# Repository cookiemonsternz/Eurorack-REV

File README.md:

# REV

_Digital reverb / delay eurorack module, user programmable and customisable._

#### What?
The next effect in a series of eurorack modules! REV is a custom digital reverb/delay processer, utilising the rp2040 mcu. Includes firmware for a basic algorithmic reverb, completely configurable via software. Default configuration uses 60kb of sram out of 264kb max. 

In terms of controls, REV features two potentiometers and 3 switches, which are by default configured to control reverb length and mix, with the switches adjusting brightness, density and stereo mixing.

#### Why?
Reverb is a very widely used effect, and arguably one of the most important in synthesizers. It sounds pretty cool but is unfortunately quite tricky to do completely analog. This module aims to provide a convenient and open source base to not only use as a reverb module, but also to prototype other digital effects.

I personally decided to make it due to my frustration with constantly having to lug around my laptop whenever I wanted reverb on my synth (which doesn't have an in-built fx section). A eurorack module is much more convenient. Having it be my own hardware allows for much more customisation than off the shelf modules / pedals, which I find very attractive.

#### How to use?
REV is a stereo board, it has an input and output for left and right, and the controls are all labelled.

In terms of getting it set up, you'll need to program the rp2040. To do this, bridge J4, which will allow you to program the flash, and then plug in the usb port. The rp2040 should show up as USB Mass Storage Device. Copy the uf2 file from the releases tab folder into the device and then disconnect J4 and unplug the usb. When you power it up via the eurorack power connector (not usb) the module should be functional.

## Renders

## Schematics

## Zine Page

## BOM
_Needed is how many I personally need :)_
| Part                                 | Quantity | Needed | Source     | Link                                                                      | Lot / Min Amount | Unit    | Net     | Running |
|--------------------------------------|----------|--------|------------|---------------------------------------------------------------------------|------------------|---------|---------|---------|
| **Capacitors**                           |          |        |            |                                                                           |                  |         |         |         |
| 100n Cap, 0805                       | 19       | 19     | JLCPCB     | https://jlcpcb.com/partdetail/YAGEO-CC0805KRX7R9BB104/C49678              | 1                | $0.0094 | $0.1786 | $0.18   |
| 1u Cap, 0805                         | 2        | 2      | JLCPCB     | https://jlcpcb.com/partdetail/29074-CL21B105KBFNNNE/C28323                | 1                | $0.0190 | $0.0380 | $0.22   |
| 10u Cap, 0805                        | 4        | 4      | JLCPCB     | https://jlcpcb.com/partdetail/16532-CL21A106KAYNNNE/C15850                | 1                | $0.0472 | $0.1888 | $0.41   |
| 47u Cap, 0805                        | 2        | 2      | JLCPCB     | https://jlcpcb.com/partdetail/17464-CL21A476MQYNNNE/C16780                | 1                | $0.0921 | $0.1842 | $0.59   |
| 10u Electrolytic Cap, D4.0xP1.5      | 2        | 0      | LCSC       | https://www.lcsc.com/product-detail/C88726.html                           | 10               | $0.0564 | $0.5600 | $1.15   |
| 22u Tantalum Cap, CASE-A-3216-18(mm) | 2        | 2      | LCSC       | https://www.lcsc.com/product-detail/C11366.html                           | 1                | $0.2379 | $0.4758 | $1.63   |
| **Resistors**                            |          |        |            |                                                                           |                  |         |         |         |
| 22? Resistor, 0805                   | 2        | 2      | JLCPCB     | https://jlcpcb.com/partdetail/18249-0805W8F220JT5E/C17561                 | 1                | $0.0027 | $0.0054 | $1.63   |
| 100? Resistor, 0805                  | 2        | 2      | JLCPCB     | https://jlcpcb.com/partdetail/18096-0805W8F1000T5E/C17408                 | 1                | $0.0023 | $0.0046 | $1.64   |
| 220? Resistor, 0805                  | 2        | 2      | JLCPCB     | https://jlcpcb.com/partdetail/18245-0805W8F2200T5E/C17557                 | 1                | $0.0031 | $0.0062 | $1.64   |
| 3.9k? Resistor, 0805                 | 2        | 2      | JLCPCB     | https://jlcpcb.com/partdetail/18302-0805W8F3901T5E/C17614                 | 1                | $0.0031 | $0.0062 | $1.65   |
| 10k? Resistor, 0805                  | 5        | 5      | JLCPCB     | https://jlcpcb.com/partdetail/18102-0805W8F1002T5E/C17414                 | 1                | $0.0029 | $0.0145 | $1.66   |
| 1M? Resistor, 0805                   | 2        | 2      | JLCPCB     | https://jlcpcb.com/partdetail/18202-0805W8F1004T5E/C17514                 | 1                | $0.0024 | $0.0048 | $1.67   |
| **Other**                                |          |        |            |                                                                           |                  |         |         |         |
| Schottky Diode, SOD-323              | 2        | 2      | JLCPCB     | https://jlcpcb.com/partdetail/GuangdongHottech-1N5819WS/C191023           | 1                | $0.0111 | $0.0222 | $1.69   |
| PJ301M-12 Jacks                      | 4        | 0      | Aliexpress | www.aliexpress.com/item/1005004864182675.html                             | 10               | $4.4000 | $0.0000 | $1.69   |
| RK09K 100k Potentiometer             | 2        | 0      | Aliexpress | https://www.aliexpress.com/item/1005007278123055.html                     | 5                | $1.0400 | $0.0000 | $1.69   |
| TL072CDT                             | 1        | 1      | JLCPCB     | https://jlcpcb.com/partdetail/STMicroelectronics-TL072CDT/C6961           | 1                | $0.1568 | $0.1568 | $1.85   |
| X322512MSB4SI 12MHz Crystal          | 1        | 1      | JLCPCB     | https://jlcpcb.com/partdetail/YXC_CrystalOscillators-X322512MSB4SI/C9002  | 1                | $0.0740 | $0.0740 | $1.92   |
| 74HC04D Logic Inverter               | 1        | 1      | JLCPCB     | https://jlcpcb.com/partdetail/Nexperia-74HC04D653/C5590                   | 1                | $0.1521 | $0.1521 | $2.07   |
| W25Q128JVS Flash                     | 1        | 1      | JLCPCB     | https://jlcpcb.com/partdetail/WinbondElec-W25Q128JVSIQ/C97521             | 1                | $2.6146 | $2.6146 | $4.69   |
| AMS1117-3.3 LDO                      | 2        | 2      | JLCPCB     | https://jlcpcb.com/partdetail/Advanced_MonolithicSystems-AMS1117_33/C6186 | 1                | $0.2024 | $0.4048 | $5.09   |
| RP2040 MCU                           | 1        | 1      | JLCPCB     | https://jlcpcb.com/partdetail/RaspberryPi-RP2040/C2040                    | 1                | $0.9843 | $0.9843 | $6.08   |
| IDC Connector                        | 1        | 0      | LCSC       | https://www.lcsc.com/product-detail/C7430313.html                         | 5                | $0.0834 | $0.0000 | $6.08   |
| USB B Micro Port                     | 1        | 1      | JLCPCB     | https://jlcpcb.com/partdetail/SHOUHAN-MicroXNJ/C404969                    | 1                | $0.0406 | $0.0406 | $6.12   |
| SPDT Switch                          | 3        | 0      | Aliexpress | https://www.aliexpress.com/item/1005005370002265.html                     | 5                | $0.8520 | $0.0000 | $6.12   |
| **Non-Components**                       |          |        |            |                                                                           |                  |         |         |         |
| Aluminium Plate (100x200x2mm)        | 1        | 1      | Aliexpress | https://www.aliexpress.com/item/1005007160296738.html                     | 1                | $6.2300 | $6.2300 | $12.35  |
| PCB                                  | 1        | 1      | JLCPCB     | NA                                                                        | 5                | $0.8200 | $4.1000 | $16.45  |
| **Total**                                |          |        |            |                                                                           |                  |         |         | $16.45  |

| Totals                          | Money  |
|---------------------------------|--------|
| Aliexpress, Inc. Shipping + Tax | $7.35  |
| JLCPCB, Inc. Shipping + Tax     | $41.21 |
| **Total**                           | $48.56 |

## CAD Links
Heres the links to the CAD source, Onshape:
[Panel source](https://cad.onshape.com/documents/1214f87d69295045284472ae/w/920e2a43c1f3f44d8378acda/e/9f1143cafdcad0010397ac9a)

## Directory Structure
- **hardware/**
    - **bom/** - BOM Files (CSV and LibreOffice Calc)
    - **cad/** - CAD Files
        - **render/** - Files for rendering (inc. gltf models)
    - **rev/** - KiCad files
        - **lib/** - External libraries
        - **production/** - Production files (Gerber, etc.)
        - **plots/** - Schematic plot
- **journals/**
- **zine/** - Zine page

## References
[RP2040 Hardware Guide](https://pip-assets.raspberrypi.com/categories/814-rp2040/documents/RP-008279-DS-1-hardware-design-with-rp2040.pdf)

#### This project was created for [Hack Club](https://hackclub.com/) - [Fallout](https://fallout.hackclub.com/)

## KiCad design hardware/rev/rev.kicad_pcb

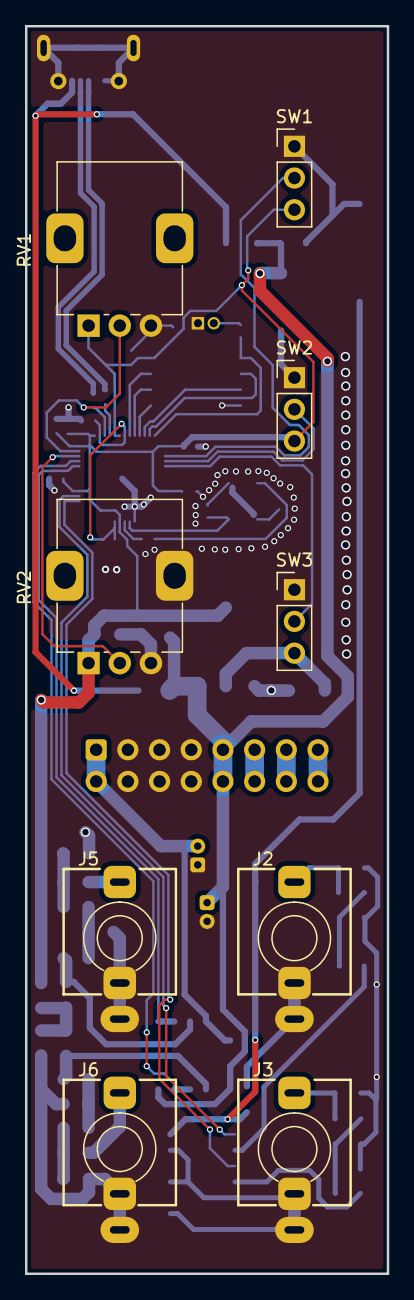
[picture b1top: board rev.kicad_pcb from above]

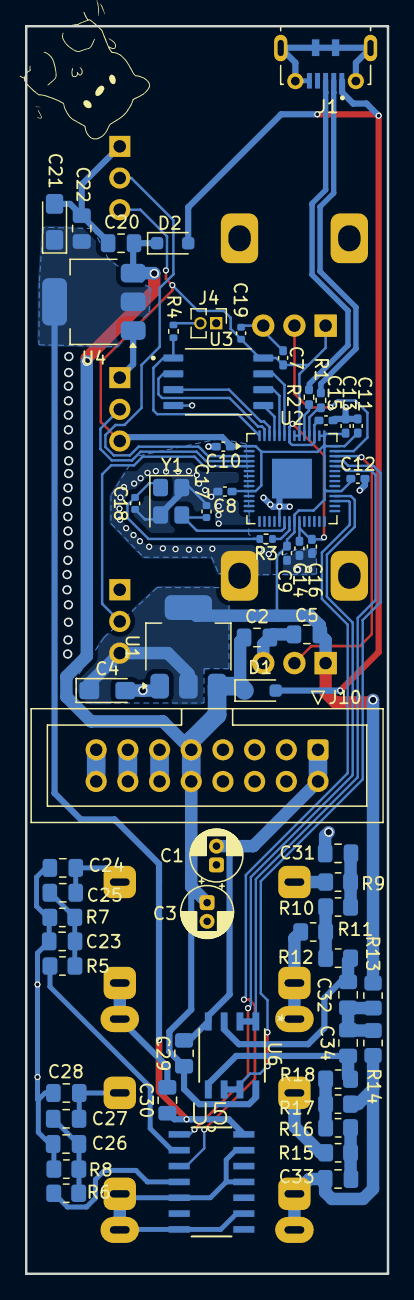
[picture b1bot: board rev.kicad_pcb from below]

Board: 2 copper layers, 29.0 x 100.0 mm, 72 parts (63 on the bottom side), 45 nets.

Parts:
C1, C3: 10u; CP_Radial_D4.0mm_P1.50mm
C2, C5, C20, C22: 10u; C_0805_2012Metric_Pad1.18x1.45mm_HandSolder
C4, C21: 22u; CP_EIA-3216-18_Kemet-A_HandSolder
C7, C8, C9, C10, C11, C12, C14, C15: 100n; C_0402_1005Metric_Pad0.74x0.62mm_HandSolder
C13, C16: 1u; C_0402_1005Metric_Pad0.74x0.62mm_HandSolder
C17, C18: 20p; C_0402_1005Metric
C19: 100n; C_0402_1005Metric
C23, C24, C26, C28, C29, C30, C31, C32, C33, C34: 100n; C_0805_2012Metric_Pad1.18x1.45mm_HandSolder
C25, C27: 47u; C_0805_2012Metric_Pad1.18x1.45mm_HandSolder
D1, D2: D_Schottky; D_SOD-323_HandSoldering
J1: USB_B_Micro; SHOUHAN_MICROXNJ
J2: OUT_L; Jack_3.5mm_QingPu_WQP-PJ301M-12_Vertical
J3: OUT_R; Jack_3.5mm_QingPu_WQP-PJ301M-12_Vertical
J4: Conn_01x02; PinHeader_1x02_P1.27mm_Vertical
J5: IN_L; Jack_3.5mm_QingPu_WQP-PJ301M-12_Vertical
J6: IN_R; Jack_3.5mm_QingPu_WQP-PJ301M-12_Vertical
J10: Conn_02x08_Odd_Even; IDC-Header_2x08_P2.54mm_Vertical
R1, R2: 22; R_0402_1005Metric_Pad0.72x0.64mm_HandSolder
R3, R4: 1k; R_0402_1005Metric
R5, R6: 220; R_0805_2012Metric_Pad1.20x1.40mm_HandSolder
R7, R8: 100; R_0805_2012Metric_Pad1.20x1.40mm_HandSolder
R9, R12, R15, R18: 1M; R_0805_2012Metric_Pad1.20x1.40mm_HandSolder
R10, R13, R14, R16: 10k; R_0805_2012Metric_Pad1.20x1.40mm_HandSolder
R11, R17: 3.9k; R_0805_2012Metric_Pad1.20x1.40mm_HandSolder
RV1, RV2: 100k; Potentiometer_Alps_RK09K_Single_Vertical
SW1, SW2, SW3: SW_SPDT; PinHeader_1x03_P2.54mm_Vertical
U1, U4: AMS1117-3.3; SOT-223-3_TabPin2
U2: RP2040; QFN-56-1EP_7x7mm_P0.4mm_EP3.2x3.2mm
U3: W25Q128JVS; SOIC127P790X216-8N
U5: 74HC04; SOIC127P600X175-14N
U6: TL072; D8_TEX_STM
Y1: YSX321SL 12MHz Crystal; Crystal_SMD_3225-4Pin_3.2x2.5mm

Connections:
+3.3V: C4.1, C5.1, C7.1, C8.1, C9.1, C10.1, C11.1, C12.1, C13.2, C19.1, R13.1, RV1.1, RV2.1, SW1.3 (C), SW2.3 (C), SW3.3 (C), U1.2 (VO), U2.1 (IOVDD), U2.10 (IOVDD), U2.22 (IOVDD), U2.33 (IOVDD), U2.42 (IOVDD), U2.43 (ADC_AVDD), U2.44 (VREG_VIN), U2.48 (USB_VDD), U2.49 (IOVDD), U3.8 (VCC)
+12V: C2.1, C3.1, C20.1, C29.1, D1.1 (K), D2.1 (K), J10.9, J10.10, U1.3 (VI), U4.3 (VI), U6.8 (V+)
-12V: C1.2, C29.2, J10.1, J10.2, U6.4 (V-)
/Net_USB_D+: R2.2, U2.47 (USB_DP)
/Net_USB_D-: R1.2, U2.46 (USB_DM)
/PWM_L: C24.1, C25.2, J2.T
/PWM_R: C27.2, C28.1, J3.T
AUDIO_3.3V: C21.1, C22.1, C30.1, U4.2 (VO), U5.14 (VCC)
BIAS: C32.2, C34.2, R13.2, R14.1
GND: C1.1, C2.2, C3.2, C4.2, C5.2, C7.2, C8.2, C9.2, C10.2, C11.2, C12.2, C13.1, C14.1, C15.1, C16.2, C17.2, C18.1, C19.2, C20.2, C21.2, C22.2, C23.2, C24.2, C26.2, C28.2, C30.2, C31.2, C33.2, J1.5 (GND), J1.SH (Shield), J2.S, J2.TN, J3.S, J3.TN, J4.1, J5.S, J5.TN, J6.S, J6.TN, J10.3, J10.4, J10.5, J10.6, J10.7, J10.8, R7.2, R8.2, R11.1, R14.2, R17.1, RV1.3, RV2.3, RV2.MP, SW1.1 (A), SW2.1 (A), SW3.1 (A), U1.1 (GND), U2.19 (TESTEN), U2.57 (GND), U3.4 (GND), U4.1 (GND), U5.5, U5.7 (GND), U5.9, U5.11, U5.13, Y1.2 (G), Y1.4 (G)
IN_L: U2.38 (GPIO26/ADC0), U6.1, U6.2 (-)
IN_R: U2.39 (GPIO27/ADC1), U6.6 (-), U6.7
unnamed: C18.2, R3.2, Y1.1
unnamed: C23.1, C25.1, R5.2, R7.1
unnamed: C26.1, C27.1, R6.2, R8.1
unnamed: C31.1, R9.2, R10.1
unnamed: C33.1, R15.2, R16.1
unnamed: J4.2, R4.1
unnamed: J5.T, R9.1
unnamed: J6.T, R15.1
unnamed: R5.1, U5.2
unnamed: R6.1, U5.4
unnamed: R10.2, R11.2, R12.1
unnamed: R16.2, R17.2, R18.1
unnamed: C14.2, C15.2, C16.1, U2.23 (DVDD), U2.45 (VREG_VOUT), U2.50 (DVDD)
unnamed: C32.1, R12.2, U6.3 (+)
unnamed: C34.1, R18.2, U6.5 (+)
OUT_L: U2.32 (GPIO21), U5.1
OUT_R: U2.31 (GPIO20), U5.3
POT_1: RV1.2, U2.41 (GPIO29/ADC3)
POT_2: RV2.2, U2.40 (GPIO28/ADC2)
QSPI_SCLK: U2.52 (QSPI_SCLK), U3.6 (CLK)
QSPI_SD0: U2.53 (QSPI_SD0), U3.5 (DI(IO0))
QSPI_SD1: U2.55 (QSPI_SD1), U3.2 (DO(IO1))
QSPI_SD2: U2.54 (QSPI_SD2), U3.3 (IO2)
QSPI_SD3: U2.51 (QSPI_SD3), U3.7 (IO3)
QSPI_SS: R4.2, U2.56 (~QSPI_SS), U3.1 (~CS)
SW_1: SW1.2 (B), U2.3 (GPIO1)
SW_2: SW2.2 (B), U2.4 (GPIO2)
SW_3: SW3.2 (B), U2.5 (GPIO3)
USB_D+: J1.3 (D+), R2.1
USB_D-: J1.2 (D-), R1.1
VBUS: D1.2 (A), D2.2 (A), J1.1 (VBUS)
XIN: C17.1, U2.20 (XIN), Y1.3
XOUT: R3.1, U2.21 (XOUT)

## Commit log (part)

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2026-06-04 schematic :)
2026-06-06 pcb + panel
2026-06-06 panel art + blender
